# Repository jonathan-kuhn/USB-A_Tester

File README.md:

# USB-A_Tester
A very simple PCB made to test wheter a USB-Port is providing voltage or not

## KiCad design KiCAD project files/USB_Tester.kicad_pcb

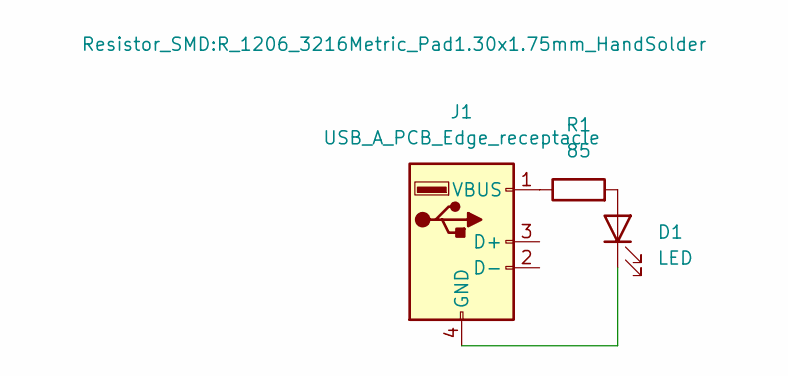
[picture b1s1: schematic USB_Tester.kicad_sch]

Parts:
D1: LED; LED_1206_3216Metric_Pad1.42x1.75mm_HandSolder
J1: USB_A_PCB_Edge_receptacle
R1: 85; R_1206_3216Metric_Pad1.30x1.75mm_HandSolder

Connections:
unnamed: D1.2 (A), R1.2
unnamed: D1.1 (K), J1.4 (GND)
unnamed: J1.1 (VBUS), R1.1

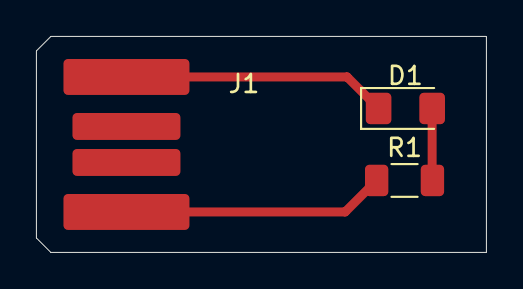
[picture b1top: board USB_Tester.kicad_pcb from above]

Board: 2 copper layers, 25.0 x 12.0 mm, 3 parts (0 on the bottom side), 3 nets.

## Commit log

2025-05-11 removed license
2025-05-11 added Gerbers as well as the Kicad project files
2025-05-11 added Gerbers, but actually now
2025-05-11 Hopefully changed the B-Silkscreen layer to include a qr-code to my channel
